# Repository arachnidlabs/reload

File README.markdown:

# Re:load #

Re:load is an adjustable dummy load with the following features:

 * No external power supply required - powered by the device under test.
 * Wide range of input voltages, from 3.3 to 30 volts.
 * Adjustable load from 0 to 3.5 amps (or 0 to 10 amps in the high current version)
 * Up to 14 watts power dissipation (40 watts in the high current version)
 * Virtually indestructible: The power FET, BTS117, has built in overtemp, ESD, and overcurrent protection. A diode protects the opamp from reverse bias.
 * Load remains constant under the whole range of input voltage.
 * Screw terminal and banana plug footprints.
 * Low BoM cost, and easy to solder thru-hole parts.
 * Test points for reading current with a voltmeter.
 
Read more about Re:load [here](http://www.arachnidlabs.com/reload/), buy the regular one [here](https://tindie.com/shops/arachnidlabs/reload-the-simple-robust-affordable-dummy-load/) and Epic Re:load [here](https://tindie.com/shops/arachnidlabs/epic-reload-the-simple-robust-powerful-adjustable-dummy-load/). Assembly and usage instructions can be found [here](http://www.arachnidlabs.com/reload/instructions.html).
 
## BoM ##

<table>
  <thead>
    <tr><th>Designation</th><th>Re:load Part</th><th>Epic Re:load part</th><th>Quantity</th></tr>
  </thead>
  <tr><th></th><td colspan="2">Re:load PCB</td><td>1</td></tr>
  <tr><th>Q1</th><td>BTS117 TO-220 MOSFET</td><td>BTS141 TO-220 MOSFET</td><td>1</td></tr>
  <tr><th></th><td>12 watt heatsink</td><td>20 watt heatsink</td><td>1</td></tr>
  <tr><th>R1</th><td colspan="2">3 watt 0.05 ohm resistor</td><td>1</td></tr>
  <tr><th>R6</th><td colspan="2">10k ohm potentiometer</td><td>1</td></tr>
  <tr><th>IC1</th><td colspan="2">MCP6002 8-DIP Op-Amp</td><td>1</td></tr>
  <tr><th>IC2</th><td colspan="2">LP2950 3.0v precision LDO regulator</td><td>1</td></tr>
  <tr><th>JP1</th><td colspan="2">2 terminal 5.0mm spring terminal</td><td>1</td></tr>
  <tr><th>D1</th><td colspan="2">BAT42 Schottky Diode</td><td>1</td></tr>
  <tr><th>C2</th><td colspan="2">33uF Electrolytic Capacitor</td><td>1</td></tr>
  <tr><th>C3</th><td colspan="2">1uF Ceramic Capacitor</td><td>1</td></tr>
  <tr><th>C1</th><td colspan="2">0.1uF Ceramic Capacitor</td><td>1</td></tr>
  <tr><th rowspan="3">R3</th><td colspan="2">510k ohm resistor</td><td>1</td></tr>
  <tr><td colspan="2">160k ohm resistor</td><td>1</td></tr>
  <tr><td colspan="2">75k ohm resistor</td><td>1</td></tr>
  <tr><th>R4, R5</th><td colspan="2">10k ohm 1% resistor</td><td>2</td></tr>
  <tr><th>R7</th><td colspan="2">100 ohm resistor</td><td>1</td></tr>
  <tr><th></th><td colspan="2">Packet of thermal paste</td><td>1</td></tr>
  <tr><th></th><td colspan="2">M3 6mm machine screw</td><td>1</td></tr>
  <tr><th></th><td colspan="2">M3 nut</td><td>1</td></tr>
</table>

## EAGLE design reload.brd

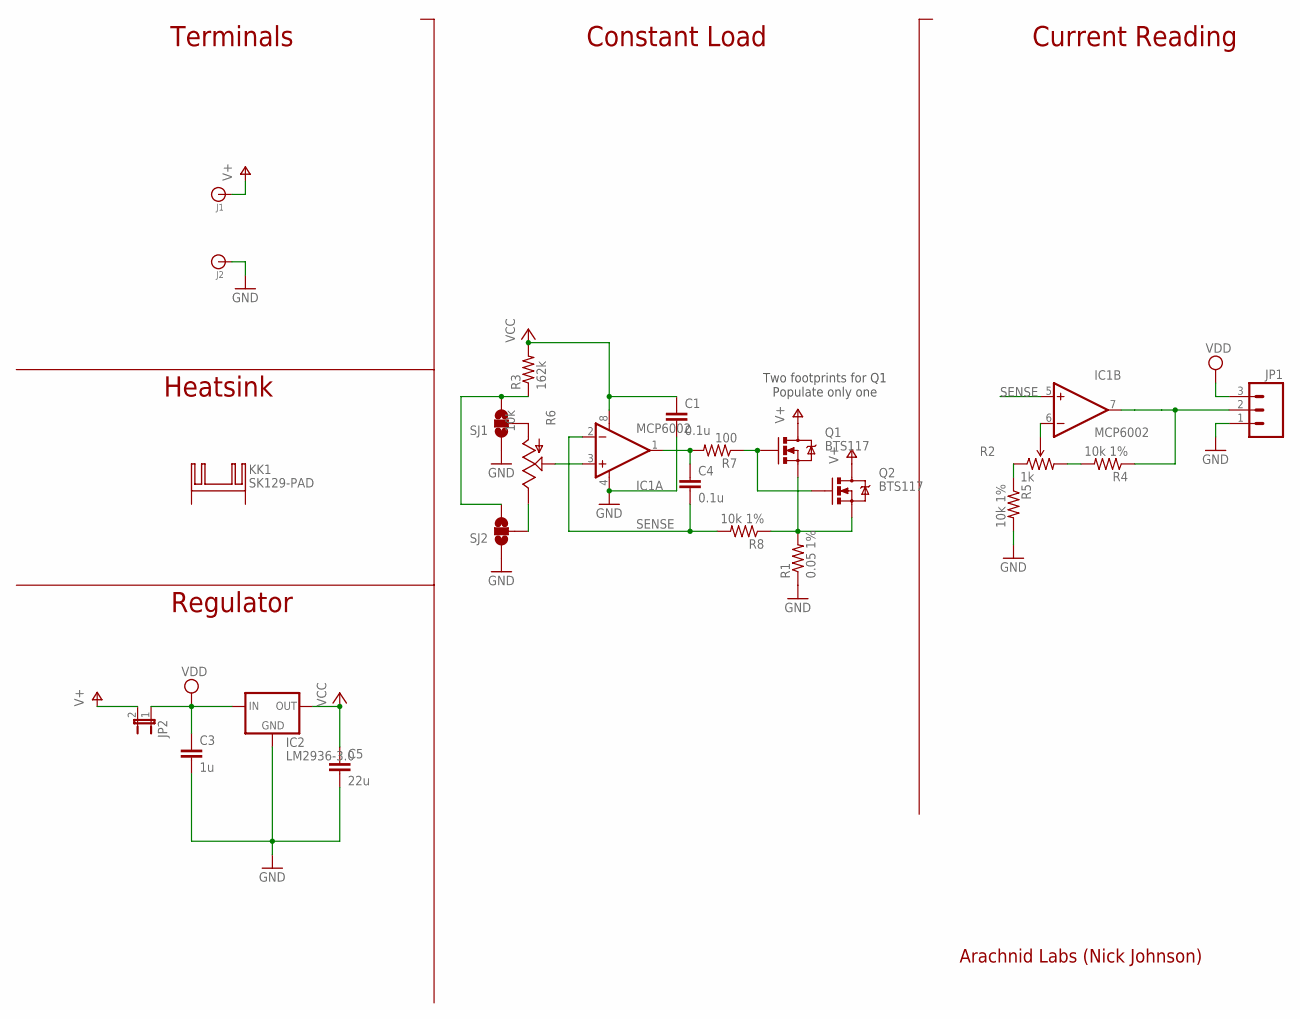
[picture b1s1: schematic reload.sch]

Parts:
C1, C4: 0.1u; 0805
C3: 1u; 0805
C5: 22u; 0805
IC1: MCP6002; SOP08
IC2: LM2936-3.0; SOT223
J1, J2: BANANA_CONN
JP1: M031X03_NO_SILK; 1X03_NO_SILK
JP2: JUMPER-2SMD-NC; SJ_2S
KK1: SK129-PAD; SK129
Q1: BTS117; TO220V
Q2: BTS117; TO220V-NOSILK
R1: 0.05 1%; R2512
R2: 1k; TRIMPOT-EVN5E
R3: 162k; 0805
R4, R5, R8: 10k 1%; 0805
R6: 10k; ALPS_POT
R7: 100; 0805
SJ1: SOLDERJUMPER_2WAYPASTE2&3; SJ_3_PASTE2&3
SJ2: SOLDERJUMPER_2WAYPASTE1&2; SJ_3_PASTE1&2

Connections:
GND: C1.2, C3.2, C5.2, IC1.4 (V-), IC2.2 (GND), J2.P$1, JP1.1, R1.1, R5.2, SJ1.1, SJ2.1
IREF: IC1.7 (OUT), JP1.2, R4.1
unnamed: C4.1, IC1.1 (OUT), R7.2
unnamed: R6.P$3 (A), SJ1.2
unnamed: Q1.3 (S), Q2.3 (S), R1.2, R8.1
unnamed: IC1.3 (+IN), R6.P$2 (S)
unnamed: IC1.6 (-IN), R2.2 (WIPER)
unnamed: R2.1 (CCW), R5.1
unnamed: R2.3 (CW), R4.2
unnamed: R6.P$1 (E), SJ2.2
unnamed: Q1.1 (G), Q2.1 (G), R7.1
unnamed: R3.1, SJ1.3, SJ2.3
SENSE: C4.2, IC1.2 (-IN), IC1.5 (+IN), R8.2
V+: J1.P$1, JP2.2, Q1.2 (D), Q2.2 (D)
VCC: C1.1, C5.1, IC1.8 (V+), IC2.3 (OUT), R3.2
VDD: C3.1, IC2.1 (IN), JP1.3, JP2.1

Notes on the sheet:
Terminals
Heatsink
Regulator
Constant Load
Current Reading
Arachnid Labs (Nick Johnson)
Two footprints for Q1 Populate only one

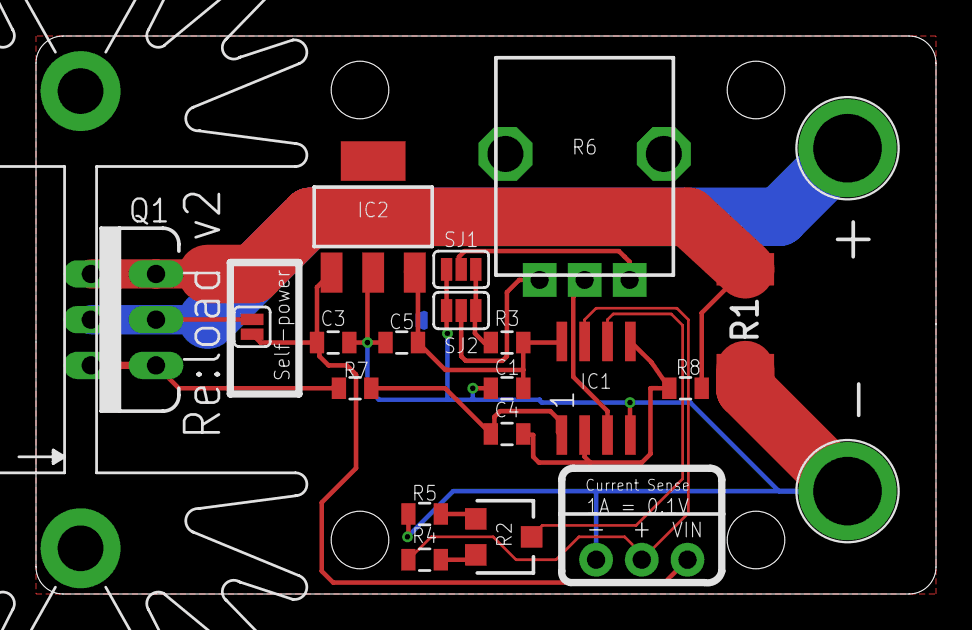
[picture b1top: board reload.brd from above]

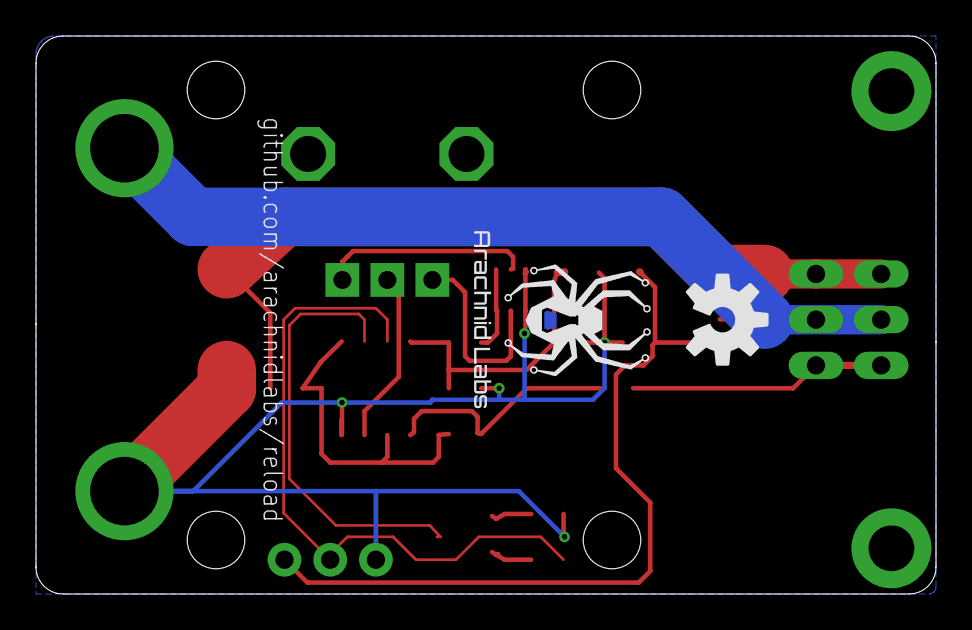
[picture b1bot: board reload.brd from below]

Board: 2 copper layers, 50.0 x 31.0 mm, 25 parts (2 on the bottom side), 16 nets.

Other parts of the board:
U$2: ARACHNID_LABS_LOGO_SM
U$3: OSHW-LOGO-M

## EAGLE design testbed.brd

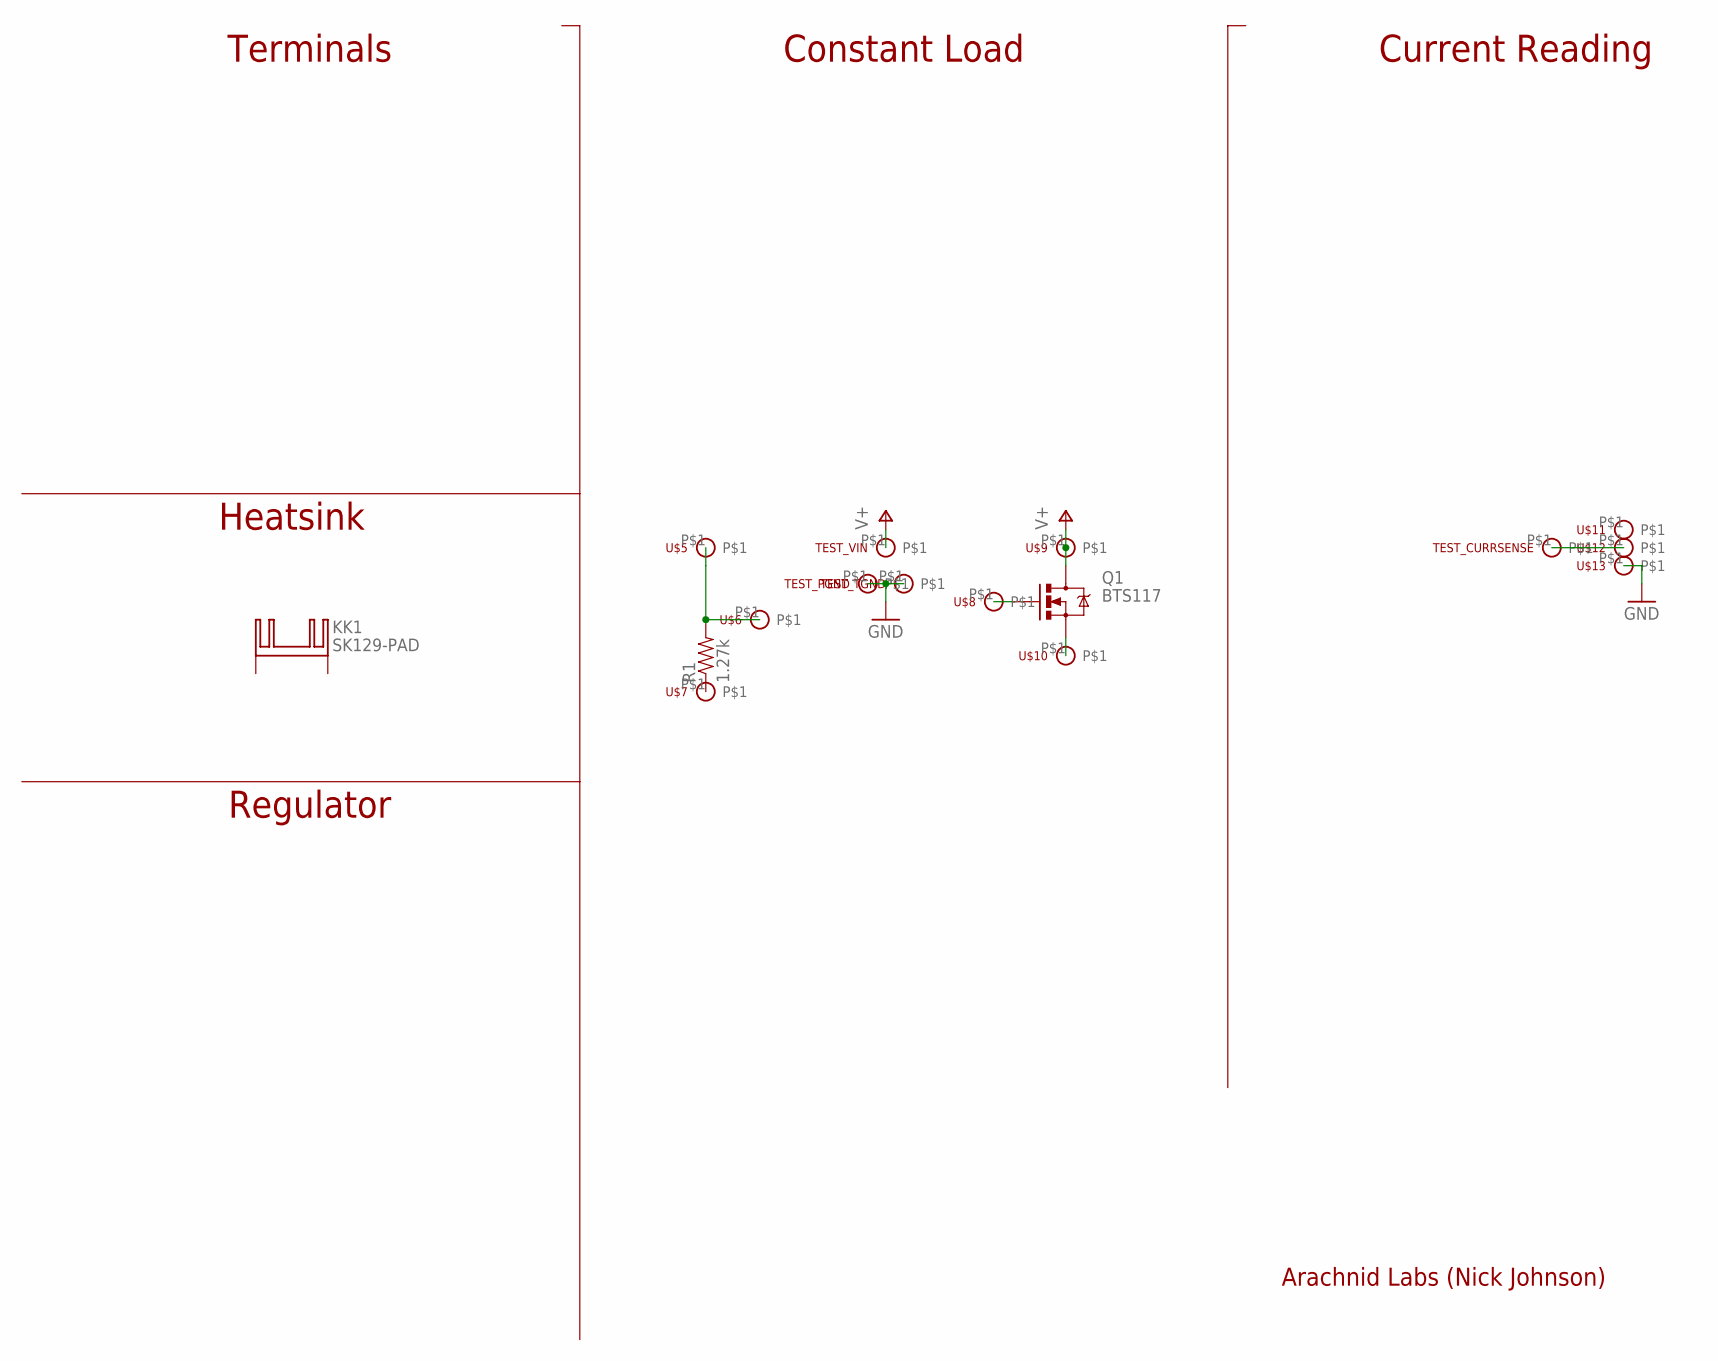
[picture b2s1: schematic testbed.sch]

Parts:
KK1: SK129-PAD; SK129
Q1: BTS117; TO220V
R1: 1.27k; 0805
TEST_CURRSENSE: TEST_POINT
TEST_PGND: TEST_POINT
TEST_TGND: TEST_POINT
TEST_VIN: TEST_POINT
U$5, U$6, U$7, U$8, U$9, U$10, U$11, U$12, U$13: POGOPIN1.02; POGOPIN-1.02

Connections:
GND: TEST_PGND.P$1, TEST_TGND.P$1, U$13.P$1
unnamed: Q1.1 (G), U$8.P$1
unnamed: TEST_CURRSENSE.P$1, U$12.P$1
unnamed: Q1.3 (S), U$10.P$1
unnamed: R1.2, U$5.P$1, U$6.P$1
unnamed: R1.1, U$7.P$1
V+: Q1.2 (D), TEST_VIN.P$1, U$9.P$1

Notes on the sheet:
Terminals
Heatsink
Regulator
Constant Load
Current Reading
Arachnid Labs (Nick Johnson)

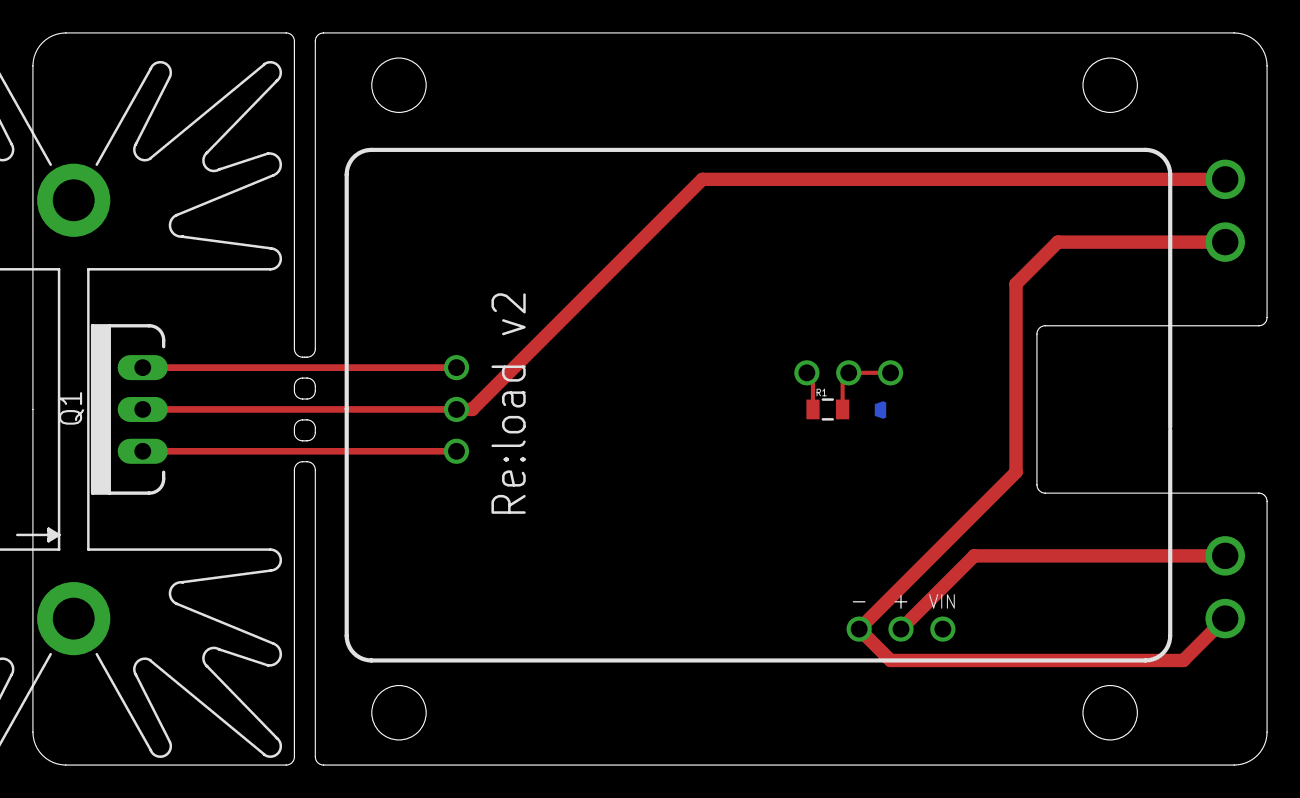
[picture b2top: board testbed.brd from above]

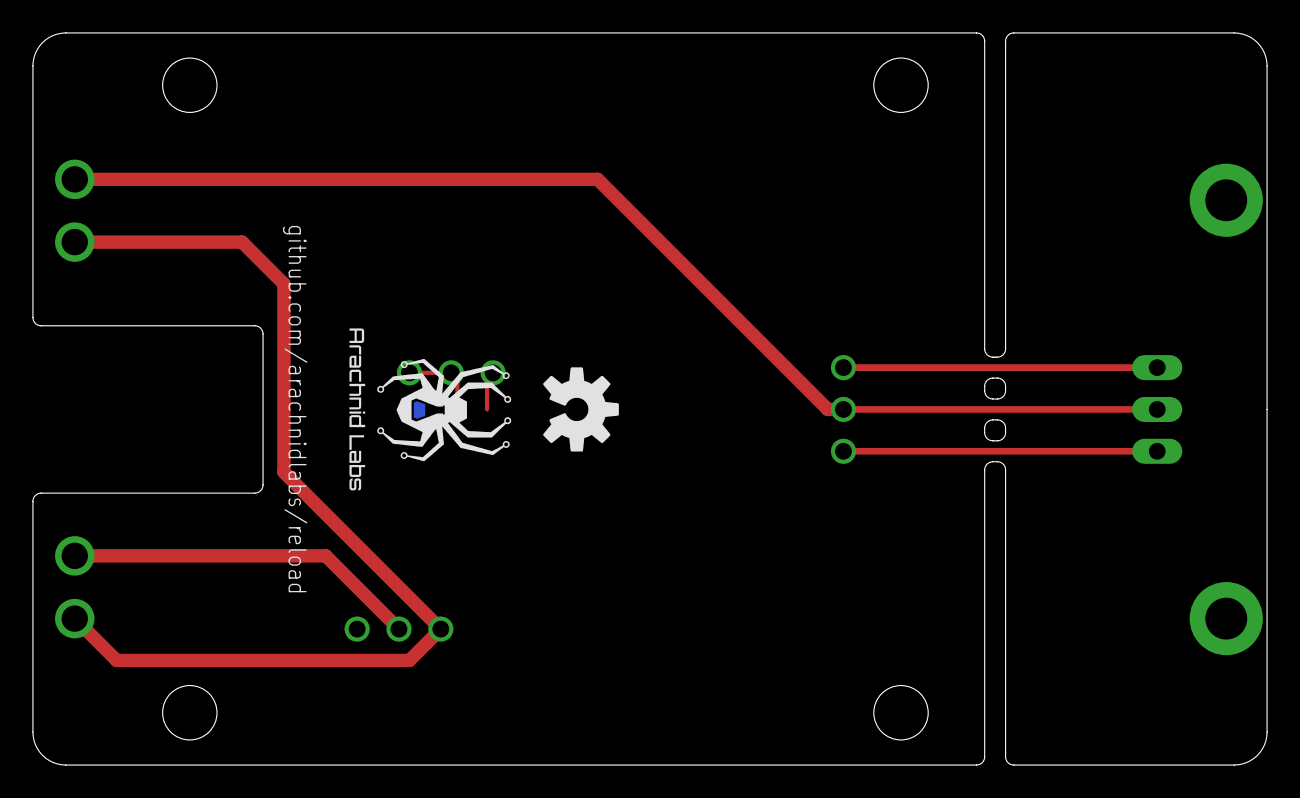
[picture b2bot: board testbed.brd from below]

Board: 2 copper layers, 74.9 x 44.5 mm, 22 parts (2 on the bottom side), 7 nets.

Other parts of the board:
U$1, U$4, U$14, U$15: STAND-OFF
U$2: ARACHNID_LABS_LOGO_SM
U$3: OSHW-LOGO-M

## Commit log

2013-01-05 Initial commit.
2013-01-05 Updated schematic, layout tweak.
2013-01-05 Generated gerbers; minor layout/schematic tweaks.
2013-01-06 Reworked to use a voltage regulator, added reverse protection diode, other improvements.
2013-01-06 Added trimpot on back side of board; minor other layout tweaks.
2013-01-06 Added readme.
2013-01-06 Fix readme BoM list.
2013-01-06 More markdown fixes.
2013-01-06 Yet more BoM tweaks.
2013-01-06 Added a second BoM for 10A version.
2013-01-07 Added series resistor for FET output.
2013-02-05 Tweaks to schematic.
2013-02-05 Improved schematic layout.
2013-02-06 Board rearrangement for spring terminals, better pot placement.
2013-02-06 Silkscreen tweaks.
2013-02-06 More silkscreen changes, added logo.
2013-02-19 Tweaks to production version of reload
2013-02-19 Updated readme.
2013-04-01 SMD respin
2013-05-08 Respin with SMD parts
2013-05-23 Changes to SMD re:load v2; added test fixture
2013-05-25 Layout tweaks and updated images
2013-09-28 Tweaks and new Re:load images
2013-10-16 Added complete technical BoM and updated schematic as so politely suggested by a commenter

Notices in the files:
parts and their libraries:
SparkFun-Passives: Licensing: CC v3.0 Share-Alike You are welcome to use this library for commercial purposes.
SparkFun-Aesthetics: Released under the Creative Commons
SparkFun-Aesthetics: http://creativecommons.org/licenses/by-sa/3.0
